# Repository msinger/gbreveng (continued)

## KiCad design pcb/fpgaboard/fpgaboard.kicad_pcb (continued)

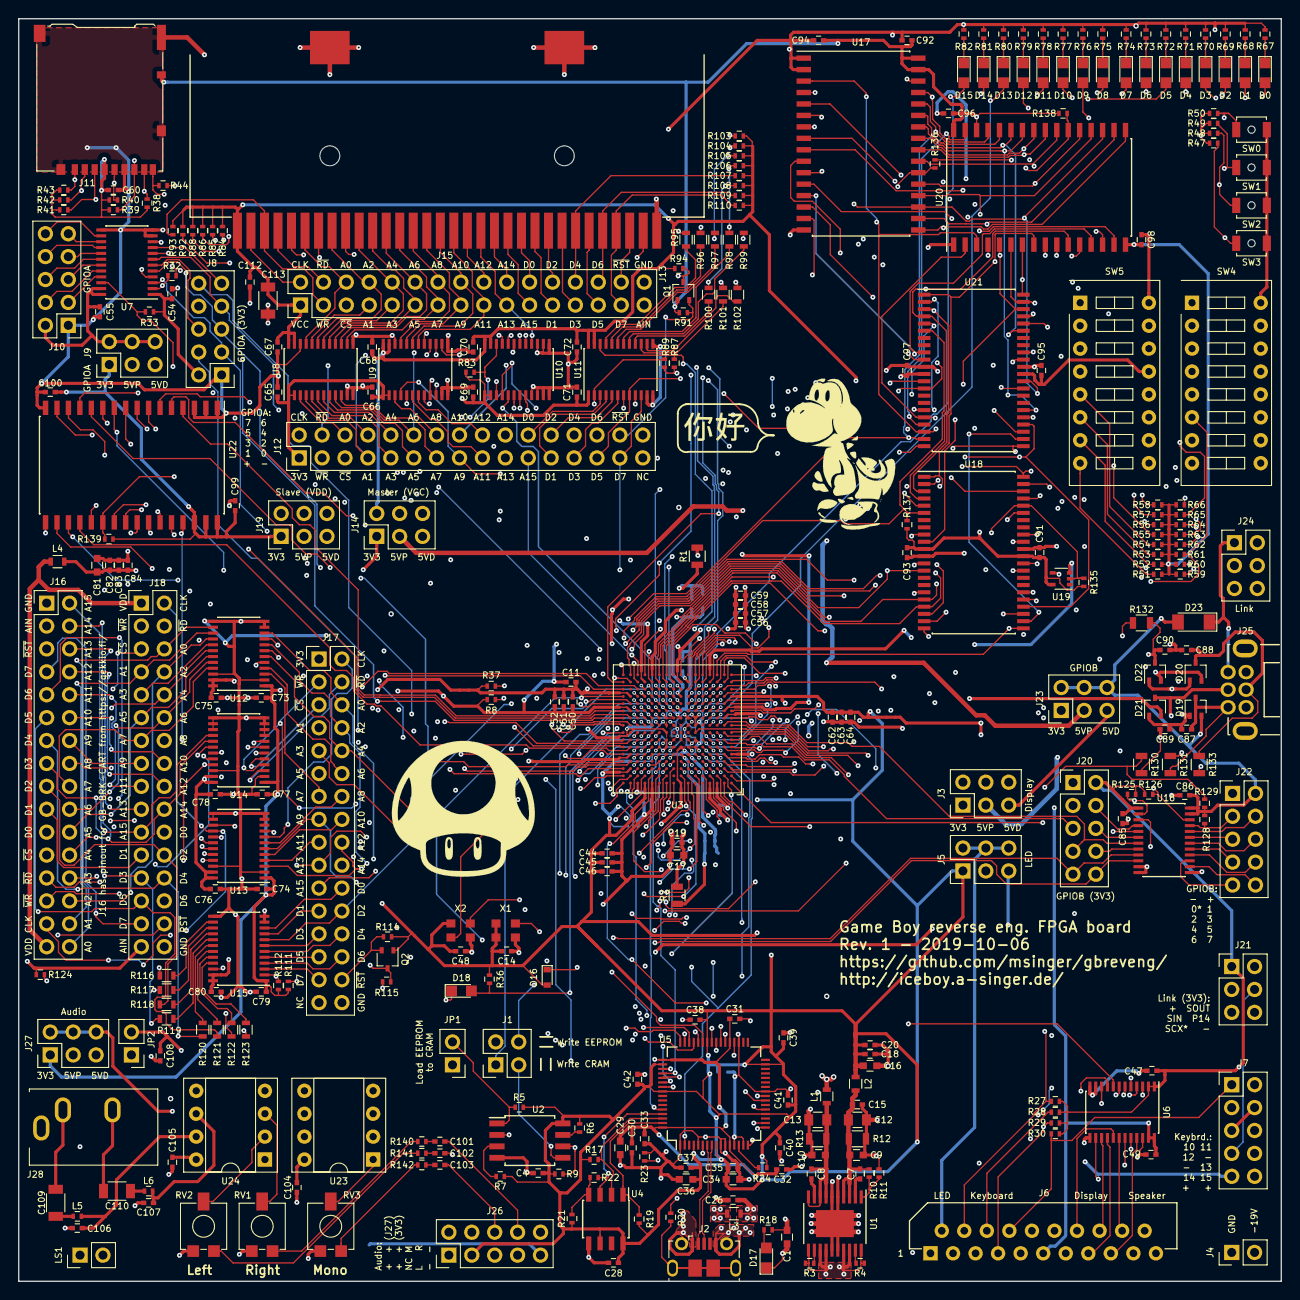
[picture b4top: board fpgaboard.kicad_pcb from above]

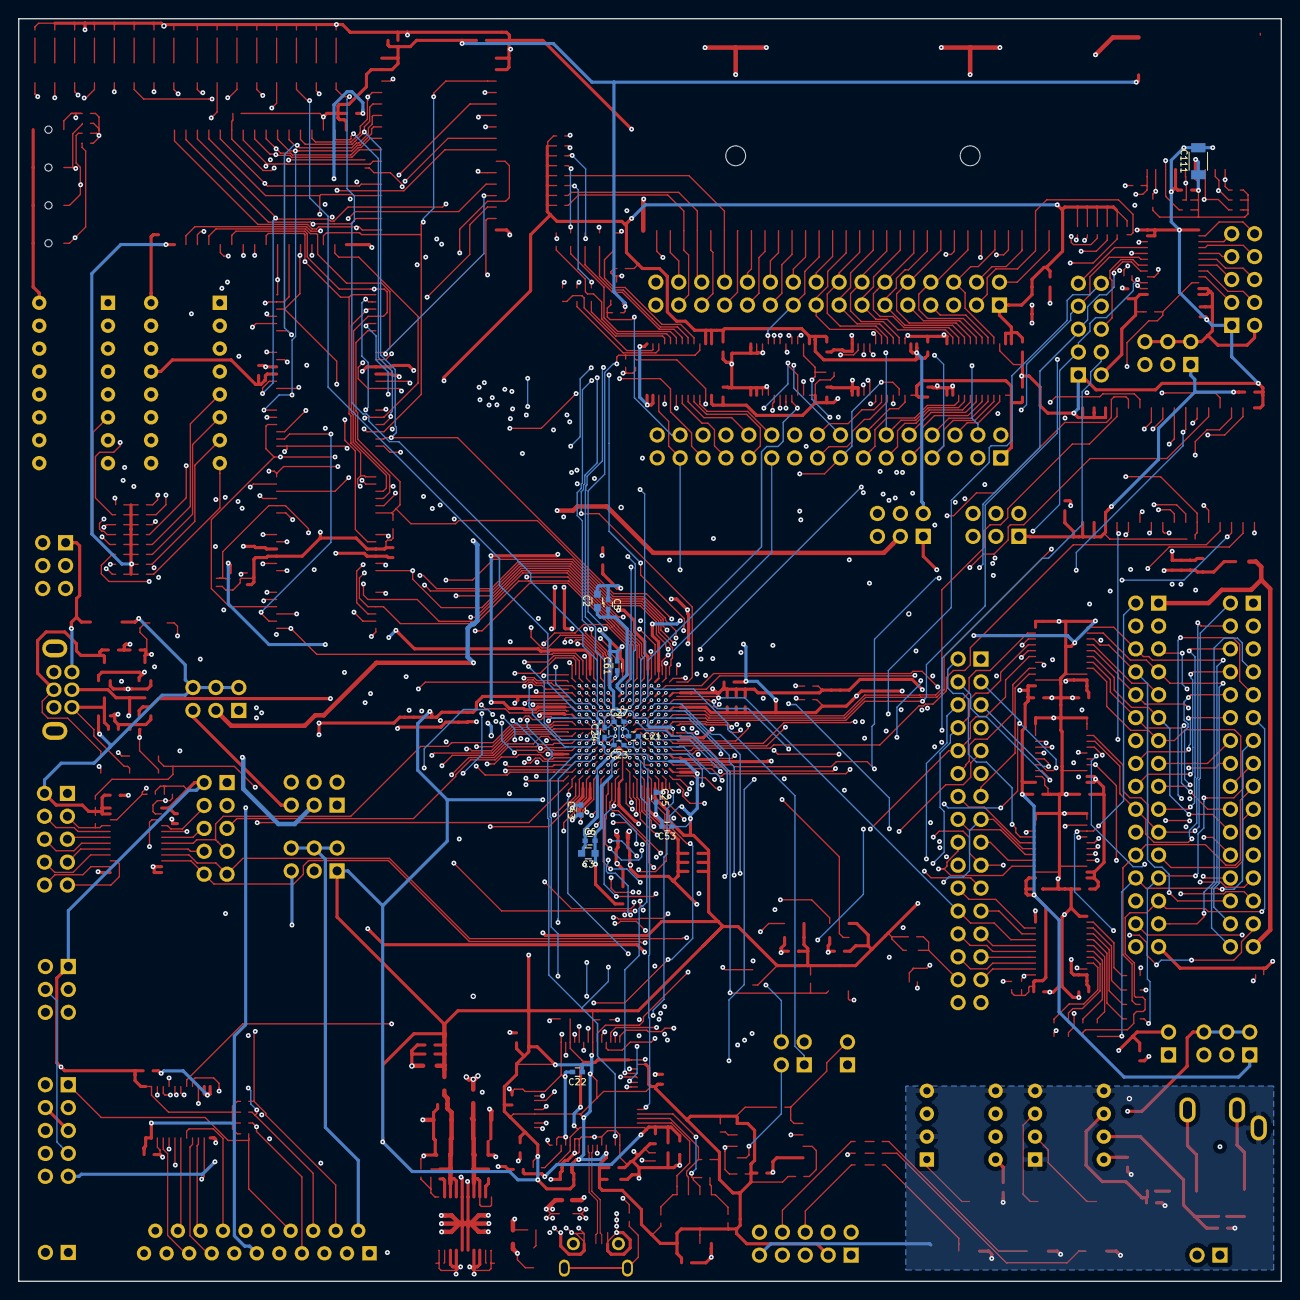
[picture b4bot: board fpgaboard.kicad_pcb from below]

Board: 4 copper layers, 140.0 x 140.0 mm, 342 parts (14 on the bottom side), 391 nets.

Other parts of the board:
G1: Yoshi
G2: hello
G3: shroom

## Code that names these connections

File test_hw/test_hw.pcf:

# For the Game Boy reverse eng. FPGA board

# Clock & Reset
set_io clk12m      J3
set_io clk16m      C8
set_io clk16m_en   F9

# LEDs
set_io led[0]      N4
set_io led[1]      R1
set_io led[2]      M5
set_io led[3]      P2
set_io led[4]      M4
set_io led[5]      P1
set_io led[6]      N3
set_io led[7]      L5
set_io led[8]      M3
set_io led[9]      M6
set_io led[10]     N2
set_io led[11]     L7
set_io led[12]     M2
set_io led[13]     K5
set_io led[14]     L3
set_io led[15]     L6

# Switches
set_io sw[0]       K3
set_io sw[1]       K1
set_io sw[2]       E2
set_io sw[3]       H5
set_io sw[4]       E3
set_io sw[5]       G4
set_io sw[6]       D1
set_io sw[7]       G5
set_io sw[8]       D2
set_io sw[9]       F4
set_io sw[10]      C2
set_io sw[11]      C1
set_io sw[12]      B1
set_io sw[13]      J1
set_io sw[14]      K11
set_io sw[15]      P13

# Buttons
set_io btn[0]      M1
set_io btn[1]      K4
set_io btn[2]      L1
set_io btn[3]      L4

# FT245 parallel FIFO
set_io ft245_d[0]  B10
set_io ft245_d[1]  B12
set_io ft245_d[2]  B13
set_io ft245_d[3]  A15
set_io ft245_d[4]  A16
set_io ft245_d[5]  B14
set_io ft245_d[6]  B15
set_io ft245_d[7]  C14
set_io ft245_n_rxf D13
set_io ft245_n_txe E10
set_io ft245_n_rd  D11
set_io ft245_n_wr  C11
set_io ft245_siwu  C13

# Audio PWMs
set_io chl         B2
set_io chr         E4
set_io chm         F5

# Joypad
set_io p10         C3
set_io p11         D3
set_io p12         E5
set_io p13         D4
set_io p14         B3
set_io p15         C4

# Master Address Bus
set_io madr[0]     L10
set_io madr[1]     R10
set_io madr[2]     T9
set_io madr[3]     N9
set_io madr[4]     P7
set_io madr[5]     T8
set_io madr[6]     T7
set_io madr[7]     L9
set_io madr[8]     T6
set_io madr[9]     P8
set_io madr[10]    T5
set_io madr[11]    M8
set_io madr[12]    P6
set_io madr[13]    N7
set_io madr[14]    T3
set_io madr[15]    R5
set_io madr[16]    P10
set_io madr[17]    N10
set_io madr[18]    T10
set_io madr[19]    T11
set_io madr[20]    T15

# Master Data Bus
set_io mdata[0]    R3
set_io mdata[1]    P5
set_io mdata[2]    T2
set_io mdata[3]    N5
set_io mdata[4]    R2
set_io mdata[5]    P4
set_io mdata[6]    T1
set_io mdata[7]    N6

# Master R/W
set_io n_mrd       R6
set_io n_mwr       M9
set_io n_prog      R9

# Master Chip Selects
set_io n_mcs_rom   T14 # A15 (ROM CS) on cartridge connector
set_io n_mcs_xram  M11 # nCS (RAM CS) on cartridge connector
set_io n_mcs_wram  R16 # WRAM
set_io n_mcs_crom  N12 # onboard cartridge ROM
set_io n_mcs_cram  L11 # onboard cartridge RAM

# Master Clock & Reset
set_io mphi        K9
set_io n_mreset    R4

# Master Bus Level Shifters
set_io n_moe       P9  # output enable for n_mrd, n_mwr, n_mcs_xram, n_mcs_rom and madr[14:13]
set_io n_moed      M7  # output enable for mdata[7:0]
set_io mdir        T13 # direction for mdata[7:0]

# Slave Address Bus
set_io adr[0]      A6
set_io adr[1]      D7
set_io adr[2]      C6
set_io adr[3]      B6
set_io adr[4]      B7
set_io adr[5]      C7
set_io adr[6]      D9
set_io adr[7]      E9
set_io adr[8]      C9
set_io adr[9]      D10
set_io adr[10]     A11
set_io adr[11]     A10
set_io adr[12]     C10
set_io adr[13]     B11
set_io adr[14]     A7

# Slave Data Bus
set_io data[0]     M14
set_io data[1]     L12
set_io data[2]     N16
set_io data[3]     L13
set_io data[4]     L14
set_io data[5]     K12
set_io data[6]     M16
set_io data[7]     J10

# Slave R/W
set_io n_rd        D8
set_io n_wr        A9

# Slave Chip Selects
set_io n_cs_rom    B8  # A15 (ROM CS) on cartridge connector
set_io n_cs_xram   M15 # nCS (RAM CS) on cartridge connector

# Slave Clock & Reset
set_io phi         F7
set_io n_reset     J11

# Slave Bus Level Shifters
set_io n_soe       P16
set_io sdir        P14

# VRAM Address Bus
set_io vadr[0]     E16
set_io vadr[1]     G13
set_io vadr[2]     D16
set_io vadr[3]     G12
set_io vadr[4]     F14
set_io vadr[5]     F12
set_io vadr[6]     D15
set_io vadr[7]     F11
set_io vadr[8]     C16
set_io vadr[9]     F13
set_io vadr[10]    B16
set_io vadr[11]    E13
set_io vadr[12]    L16
set_io vadr[13]    K13

# VRAM Data Bus
set_io vdata[0]    G16
set_io vdata[1]    H12
set_io vdata[2]    G15
set_io vdata[3]    G10
set_io vdata[4]    F16
set_io vdata[5]    G11
set_io vdata[6]    F15
set_io vdata[7]    G14

# Master R/W & Chip Select
set_io n_vrd       D14
set_io n_vwr       E14
set_io n_vcs       J12

# GPIO A
set_io pa[0]       H11
set_io pa[1]       H13
set_io pa[2]       J16
set_io pa[3]       J13
set_io pa[4]       J14
set_io pa[5]       K16
set_io pa[6]       J15
set_io pa[7]       K14
set_io n_pa_oe     R14
set_io pa_dir      R15

# GPIO B
set_io pb[0]       G1  # External Link Port SCX
set_io pb[1]       J5
set_io pb[2]       G2
set_io pb[3]       H4
set_io pb[4]       J2
set_io pb[5]       J4
set_io pb[6]       H16
set_io pb[7]       H14
set_io n_pb_oe     H1
set_io pb_dir      H2

# External Link Port
set_io sin         F3
set_io sout        G3

# SDCard
set_io sd_sw       K15
set_io sd_clk      M12
set_io sd_cmd      T16
set_io sd_data[0]  F1
set_io sd_data[1]  H6
set_io sd_data[2]  F2
set_io sd_data[3]  H3

# Display
set_io lcd_hsync   C5
set_io lcd_vsync   A1
set_io lcd_latch   A2
set_io lcd_altsig  D5
set_io lcd_ctrl    A5
set_io lcd_clk     B4
set_io lcd_data[0] B5
set_io lcd_data[1] E6

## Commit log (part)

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2018-11-11 add bus access table
2018-11-11 add dummy tables for DMA bus access
2018-11-11 add background color to tables based on bus type
2018-11-12 update timings comment
2018-11-13 add comments with DMA and VRAM timings
2018-11-18 new measurements
2018-11-23 added genclk code for clocking GB by FPGA
2018-11-23 print summary after ./configure
2018-11-24 glitch through FF50 write instruction
    Trophy unlocked!
    Ready to mess around with a GameBoy with mapped in boot ROM.
2018-11-25 document ff50 glitching
2019-01-20 fpga board rev. 0
2019-01-20 add BOM and iomap
2019-03-03 fix warnings
2019-04-30 port genclk to gbreveng board
2019-04-30 add template for programming FTDI EEPROM
2019-04-30 port skip_ff50 to gbreveng board
2019-05-01 port mrd_test to gbreveng board
2019-08-09 switch to next-pnr
2019-08-10 make genclk and skip_ff50 restartable
2019-08-10 cartfix PCB for patching pin swap of gbreveng J16
2019-08-10 add PCB for probing DMG display signals
2019-08-16 label all external connector pins on gbreveng brd.
2019-10-03 written down some measurements about PPU signals
2019-10-04 more PPU measurements
2019-10-05 test image generator for DMG LCD
2019-10-06 fix labeling of D0&D1 LCD signals
2019-10-09 more ppu info
2019-10-27 added labels for FT245 configuration of FTDI
2019-11-08 fix/update pin list
2019-11-09 shiva: cpu and dbg interface working
2019-11-11 shiva: implemented first counter
2019-11-17 shiva: implement comparators and signal routes
2019-11-17 shiva: move counter block into module
2019-11-18 shiva: make RAM accessible by DUT
2019-11-20 shiva: make pa0 triggerable by counters
2019-11-20 shiva: add source for always 1 signals
2019-11-22 shiva: feed irq flags with signal routes
2019-11-24 shiva: make DUT bus available to CPU
2019-11-24 shiva: document memory map
2019-12-08 fix comparator
2019-12-08 reduce peripherals to bare minimum
2019-12-08 fix lvl converter enable
2020-05-04 add connection in schematic
2020-05-09 remove wand and wor nets; yosys emits $or gates
2020-05-09 shiva: delay bus comparator signal
2020-05-10 shiva: add three more comparators for DUT bus
2020-06-05 shiva: implement bus recording
2020-06-05 shiva: more counters and routes
2020-06-05 use wor and wand again; yosys fixed it
2020-08-29 add tests for checking BGA soldering
    * test clock inputs
    * test LEDs and switches
    * test p10-15
    * test LCD pins
2020-08-29 fix some ugly PCB traces
2020-08-29 add soundfix PCB for gbreveng rev. 0
2020-08-29 add PCB for testing -19V supply for LCD bias
2020-08-30 fix VRAM read and write signal
2020-08-30 add hw tests for onboard memories
2021-05-14 Add design for dumping Wide-Boy64 AGB PROM
2021-05-16 Add Wide-Boy research document
2021-05-16 Add Wide-Boy64 AGB 40-pin conn to CPU&FPGA pin#s
2021-05-16 Finish Wide-Boy64 AGB 40-pin conn table
2021-05-18 Document more Wide-Boy64 AGB stuff
2021-05-19 Add more Wide-Boy documentation
2021-05-24 Document N64 cart conn on Wide-Boy64
2021-05-26 Fix Flash reset pin in WB64 doc
2021-08-14 Document tribuffer and flip-flop cells
2021-08-14 Add license info to some files
2021-08-14 Update information on wideboy
2021-08-14 Add quick description about DMG Cells document
2021-08-14 Add complete Wideboy 64 AGB schematic
2021-08-15 Add documentation about IOBUFFER cells
2021-08-15 Add missing wideboy picture in wideboy doc
2021-08-15 Make tribuffer cell documentation consistent
2021-08-15 Add documentation for more cells
2021-08-16 Restructure index in cell documentation
2021-08-16 Document remaining cell types
2021-08-16 Add note about inverting reset pin
2021-08-16 Add documentation about OR-AND compound gate
2021-08-17 Rename assembler and linker LR35902->SM83
2021-08-17 Update assembler files
2021-08-18 Update mem_patterns document
2021-08-18 Document WR signal from CPU
2021-08-22 Add test ROMs for STOP and HALT instructions
2021-08-22 Update documentation about XI/XO pins
2021-08-23 Fix documentation about latches
2021-08-28 CPU docs: Fix direction of pin T7 (FROM_CPU5)
2021-08-29 Fix documentation about CPU pin T14
2021-09-02 Add map links to remaining Txx CPU pins
2021-09-04 Add more map links for CPU connections
2021-09-06 Fix CPU input clock description
2021-09-09 Document CPU reset polarity
2021-09-12 List FF cell instances in documentation
2021-09-12 Document how to infer clock polarity of DFFR-B cells
2021-09-13 Improve HTML documentation for mobile
2021-09-13 Document how to infer clock polarity of DFFR-B+ cells
2021-09-13 Add min-width to imgs in cell reference
2021-09-14 Add map links to DMG cells reference
2021-09-14 Add missing map link in CPU connections doc
2021-09-14 Add list of instances for IO cells in cell reference
2021-09-14 Document how to infer clock polarity of DFFSR cells
2021-09-15 Fix OBUFFER documentation
2021-09-16 Change image for OBUFFER
2021-09-16 Fix documentation for IO buffers
2021-09-18 Simple input buffer is actually inverting
2021-09-18 Modified genclk test for testing T1 and T2
    Found out that the three inputs buffers RST, T1 and T2 of
    the DMG CPU B are all three inverting, which means that the
    reset of the DFFs ADYK, AFUR, ALEF, APUK and AFER is actually
    not working when T1 and T2 are pulled down to GND. They would
    have to be pulled up to VCC for the reset to work properly.
2021-09-18 Disable competitive pull-up resistors
    I thought my dip switches broke, but I just messed up the pull-up
    configuration. I had enebled the pull-ups inside the FPGA even though I
    have pull-downs on the PCB. :/
2021-09-19 Document the weird reset behaviour of the DMG-CPU B
2021-09-19 Add missing jpg for dmg_reset.html
2021-09-19 Document IBUFFER pull-up resistors
2021-09-19 IBUFFER cells don't have pull-ups
2021-09-19 Minor additions to cell documentation
2021-09-22 List all instances of bigger tri-states
2021-09-22 Fix tri-state buffer docs
2021-09-22 Fix input buffer docs
2021-09-23 Small fixes in cells reference
2021-09-26 Update CPU connection R7 documentation
2021-09-26 Update CPU connection R7 documentation, again
2021-09-27 Add missing map links to CPU connections doc
2021-09-27 Document all CPU connections + fixes.
2021-10-04 Implement start & stop trigger for recording
2021-10-05 Convert to SystemVerilog
2021-10-07 Convert to SystemVerilog and make more simulation friendly
2021-10-10 Mark stopped recording with bit 31
2021-10-11 Make recorder cyclic/stop-at-end-of-ram configurable
2021-10-21 Update page infos of fpgaboard KiCad files
2021-10-22 Update Wide-Boy schematic
2021-10-22 Add new index.html and pictures
2021-10-24 Fix some glitchy feedback loop
2021-10-25 Add description meta tags and some image alt texts
2021-10-30 Handle level converters with hold function properly
2021-11-04 Update Memory patterns documentation
2021-11-05 Add TODOs
2021-11-22 Fix DFFR Variant C documentation
2021-11-24 Fix compound cell docs (AOI<n> -> AO<n>)
2021-12-03 Update CPU doc for R4, R5 and R7
2022-01-29 Fix description of latches and flip flops
2022-02-07 Add CMOS circuits to cell reference
2022-02-09 Cell reference: Add links to instances on map
2022-02-10 Fix broken HTML link
2022-02-21 Add layout for inverter variants A & B
2022-03-08 Use simpler MOSFET symbols in documentation
2022-03-08 Add CMOS circuit for MUX and MUXI
2022-03-08 Document layout and schematic of TRI_INV cells
2022-03-09 Add layout for XOR and XNOR cells
2022-03-13 Add layout and schematic for tri-state buffer cell
2022-03-16 Add schematics for IO pads
2022-05-14 DMG Cells: Update pictures
2022-05-14 DMG Cells: Fix BERU, BYRY and RARO
2022-08-13 Unify ids in cell reference
2022-08-30 DMG Cells: Add missing cell GURE
2022-10-02 Rename schematic pictures from *_cmos.png to *_sch.png
2022-10-02 Add documentation for SRAM cells
2022-10-24 Cell reference: Fix cell names and links
2022-10-24 Cell reference: Escape invalid characters in URLs
2022-11-06 Fix OAI, MUX and MUXI pin names
2023-06-18 Add layouts and fixed schematics for IBUFFER cells
2023-06-20 Update images of INV_A, INV_B and NAND2, Add NAND2S
2023-07-01 Update NAND2S documentation
2023-07-09 Update cell pictures and unify some names
2023-07-09 Remove obsolete dmg_cells2.html
2023-07-09 Update cell layouts based on new pictures from @gamespec
    See https://github.com/emu-russia/dmgcpu/discussions/97
2023-07-14 Update SRAM pictures and layouts
2023-07-30 Fix some schematics in documentation
2023-07-30 Add boot ROM documentation
2023-08-04 Add schematic and layout of DFFR_A cell
2023-08-06 Add layouts and schematics for DFFR_B and DFFR_B2
    + Update description of DFFR_A, DFFR_B and DFFR_B2.
    + Update DFFR_A layout.
2023-08-08 Add layout and schematic for DFFSR cell
2023-08-10 Add layout and schematic for TFFD cell
2023-08-10 Add layout for MUX cell
    + Add missing PNG for index.html
2024-02-18 Update Wide-Boy64 documentation
2024-05-29 Add SM83 cell reference
2024-06-16 Add test ROM for sound output
2024-06-19 Migrate fpgaboard from KiCad 4 to KiCad 8
2024-06-20 Migrate other PCBs from KiCad 4 to KiCad 8
2024-06-24 dmg cell doc: Fix layout of tri_buf_if0 cell
    fixes #1
2024-07-01 Update Wide-Boy documentation
    * Add information about EEPROM content
    * Add information about flash dumping
    * Add code for flash dumping
    * Fix embarrasing spelling errors
2024-07-01 WB64: Add picture of PCB under flash
2024-08-05 Fix some undefined behavior
2024-08-19 Implement debouncing of GB cart bus signals
    This makes the white Japanese flash cartridges work in passthrough mode.
2024-09-15 Add documentation about Nintendo Power cartridge
    Uploaded here: http://iceboy.a-singer.de/doc/np_gb_memory.html
2024-09-17 Fix NP GB Memory documentation
    It seems like I made some mistakes while testing the size of the map
    region. It is actually 256 bytes, not 128. I noticed this when I was
    testing it on the flash chip in the Net de Get cartridges.
    Also I didn't include the "unprotect sector 0" command. I unlocked
    sector 0 on the two cartridges I used for testing, and then I thought
    the command isn't necessary, because everything worked without it. It
2024-09-17 Add gameboy icon to HTML docs
2024-09-23 Add link to KiCad project of NP cartridge
2024-09-23 Update NP GB Mem documentation
2024-09-24 Add reset pin description to NP GB Mem doc
2024-09-25 Update NP GB Mem doc about external oscillator
2024-09-30 Fix un-/protect sector 0 command documentation
2024-10-01 Add MMC command 0x80 to NP GB Mem doc
2024-10-01 Update host reset pin description in NP GB Mem doc
2024-10-04 Fix WP# pin in NP GB Mem doc
2024-10-05 Update info about MBC6 flash
2024-10-05 Add high-active RESET to WideBoy PROM dumper
2024-10-17 DMG Cells: Remove wrong schematics of OSC and IOC
    refs #2
2024-12-09 Fix absolute paths and some labels
2025-02-19 Add link to PROM programmer in Wide-Boy doc
2025-03-29 Ignore *.kicad_prl
2025-04-05 SM83 doc: Add doc for decoder 1&2 inverters
2025-04-12 DOC: Give more meaningful names to cell types
    Before this commit, many of the cells types in the chip were named in a
    sloppy manner. The different inverter, latch and flip flop valiants were
    just suffixed with A, B, C, D, ... Those suffixes gave no information
    about the actual differences. They had to be looked up in the
    documentation. Now the names of cell types with different variants have
    changed:
2025-04-22 Add documentation for some SM83 sequencer cells
2025-08-08 Unify DFF names in SM83 documentation
2025-08-11 Document all SM83 sequencer cells
2025-08-14 Document SM83 data bus bridge cells
2025-08-30 Document SM83 ALU cells
2025-10-22 Fix schematic in IDU0 documentation
2025-10-23 Update SM83 cell documentation
2025-10-31 Cleanup schematic of ALU_PGGEN
2025-11-01 Add missing annotation in IRQ_PRIO_BIT5 schematic
2025-11-07 Add missing SM83 cell documentation for NOR3
2025-11-11 SM83 Cells: Rename write enable inverters
2025-11-29 Update SM83 "pinout" documentation
2025-12-02 Update index.html for Visual SM83
2025-12-25 Add link to SM83 schematics
2026-02-17 DMG Cells: Update XOR, XNOR, HALF_ADD, FULL_ADD
2026-02-19 DMG Cells: Fix DFFSR schematic
2026-02-21 Fix PAD_BIDIR* cell documentation
2026-02-21 Document analog output/input pads
2026-04-06 Doc: Fix image file name
2026-04-09 Document analog cells
2026-04-10 Update DAC and MIXER symbols
2026-04-10 Add documentation for GGNMOS
2026-04-13 Cleanup main html page
